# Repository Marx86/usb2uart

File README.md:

# usb2uart
KiCAD project for HID usb to uart converter on cp2110

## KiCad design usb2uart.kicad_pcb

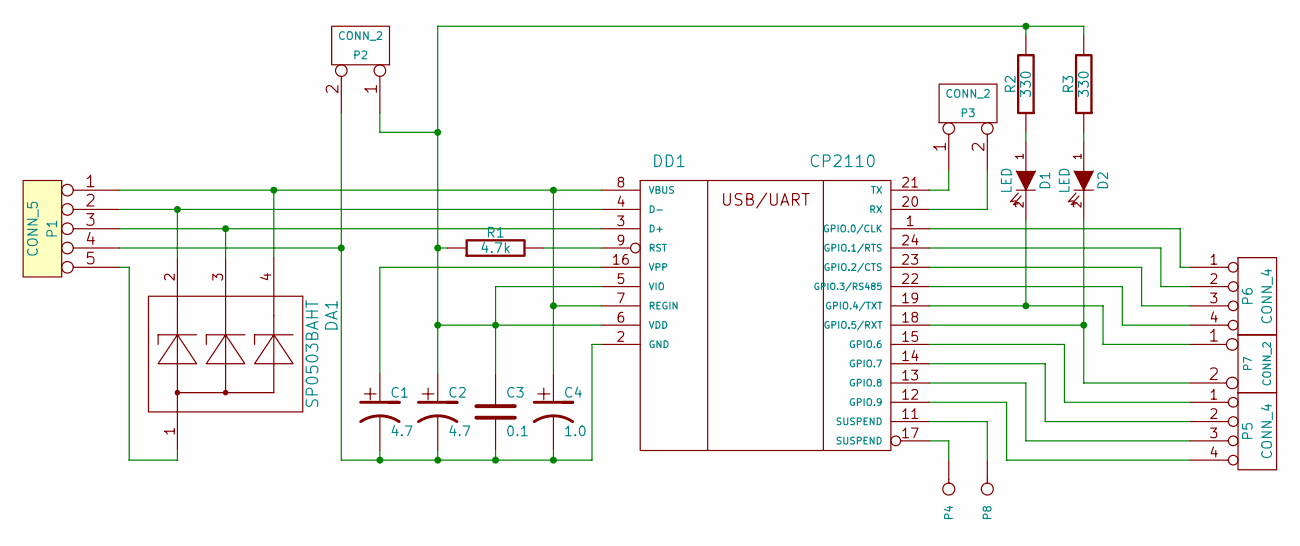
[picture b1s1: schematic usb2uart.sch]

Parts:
C1, C2: 4.7; C_Radial_D5_L6_P2.5
C3: 0.1; C_Rect_L7_W2.5_P5
C4: 1.0; C_Rect_L7_W2.5_P5
D1, D2: LED; LED-3MM
DA1: SP0503BAHT; SOT-143
DD1: CP2110; QFN-24_4x4mm_Pitch0.5mm_NoMask
P1: CONN_5; USB_B
P2, P3, P7: CONN_2; Pin_Header_Straight_1x02
P4, P8: CONN_1; Pin_Header_Straight_1x01
P5, P6: CONN_4; Pin_Header_Straight_1x04
R1: 4.7k; R_0805
R2, R3: 330; Resistor_Horizontal_RM10mm

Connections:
unnamed: C1.1, DD1.16 (VPP)
unnamed: C1.2, C2.2, C3.2, C4.2, DD1.2 (GND), P1.4, P2.2 (PM)
unnamed: C2.1, C3.1, DD1.5 (VIO), DD1.6 (VDD), P2.1, R1.1, R2.2, R3.2
unnamed: C4.1, DA1.4, DD1.7 (REGIN), DD1.8 (VBUS), P1.1
unnamed: D1.1 (A), R2.1
unnamed: D1.2 (K), DD1.19 (GPIO.4/TXT), P7.1
unnamed: D2.1 (A), R3.1
unnamed: D2.2 (K), DD1.18 (GPIO.5/RXT), P7.2 (PM)
unnamed: DA1.1, P1.5
unnamed: DA1.2, DD1.4 (D-), P1.2
unnamed: DA1.3, DD1.3 (D+), P1.3
unnamed: DD1.1 (GPIO.0/CLK), P6.1
unnamed: DD1.9 (RST), R1.2
unnamed: DD1.11 (SUSPEND), P8.1
unnamed: DD1.12 (GPIO.9), P5.4
unnamed: DD1.13 (GPIO.8), P5.3
unnamed: DD1.14 (GPIO.7), P5.2
unnamed: DD1.15 (GPIO.6), P5.1
unnamed: DD1.17 (SUSPEND), P4.1
unnamed: DD1.20 (RX), P3.2 (PM)
unnamed: DD1.21 (TX), P3.1
unnamed: DD1.22 (GPIO.3/RS485), P6.4
unnamed: DD1.23 (GPIO.2/CTS), P6.3
unnamed: DD1.24 (GPIO.1/RTS), P6.2

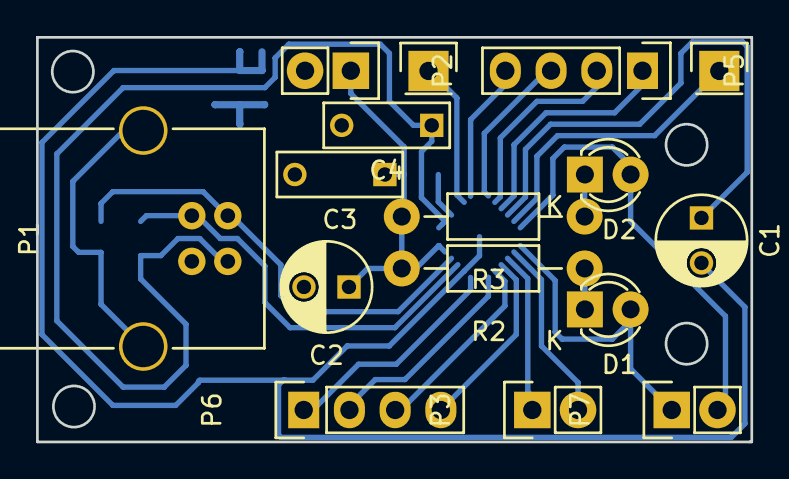
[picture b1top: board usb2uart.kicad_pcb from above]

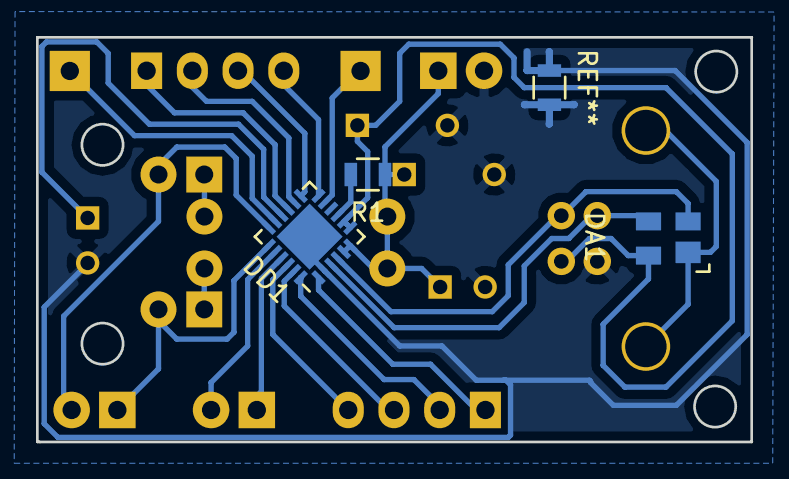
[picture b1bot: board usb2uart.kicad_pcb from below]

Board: 2 copper layers, 39.7 x 22.5 mm, 19 parts (3 on the bottom side), 24 nets.

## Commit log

2016-10-13 Add project files
2016-10-17 Create board
2016-10-18 Fix board
2016-11-15 Add test board
2016-11-18 Add mask pdf
2017-01-11 Refactoring
2017-01-11 Fix prints
